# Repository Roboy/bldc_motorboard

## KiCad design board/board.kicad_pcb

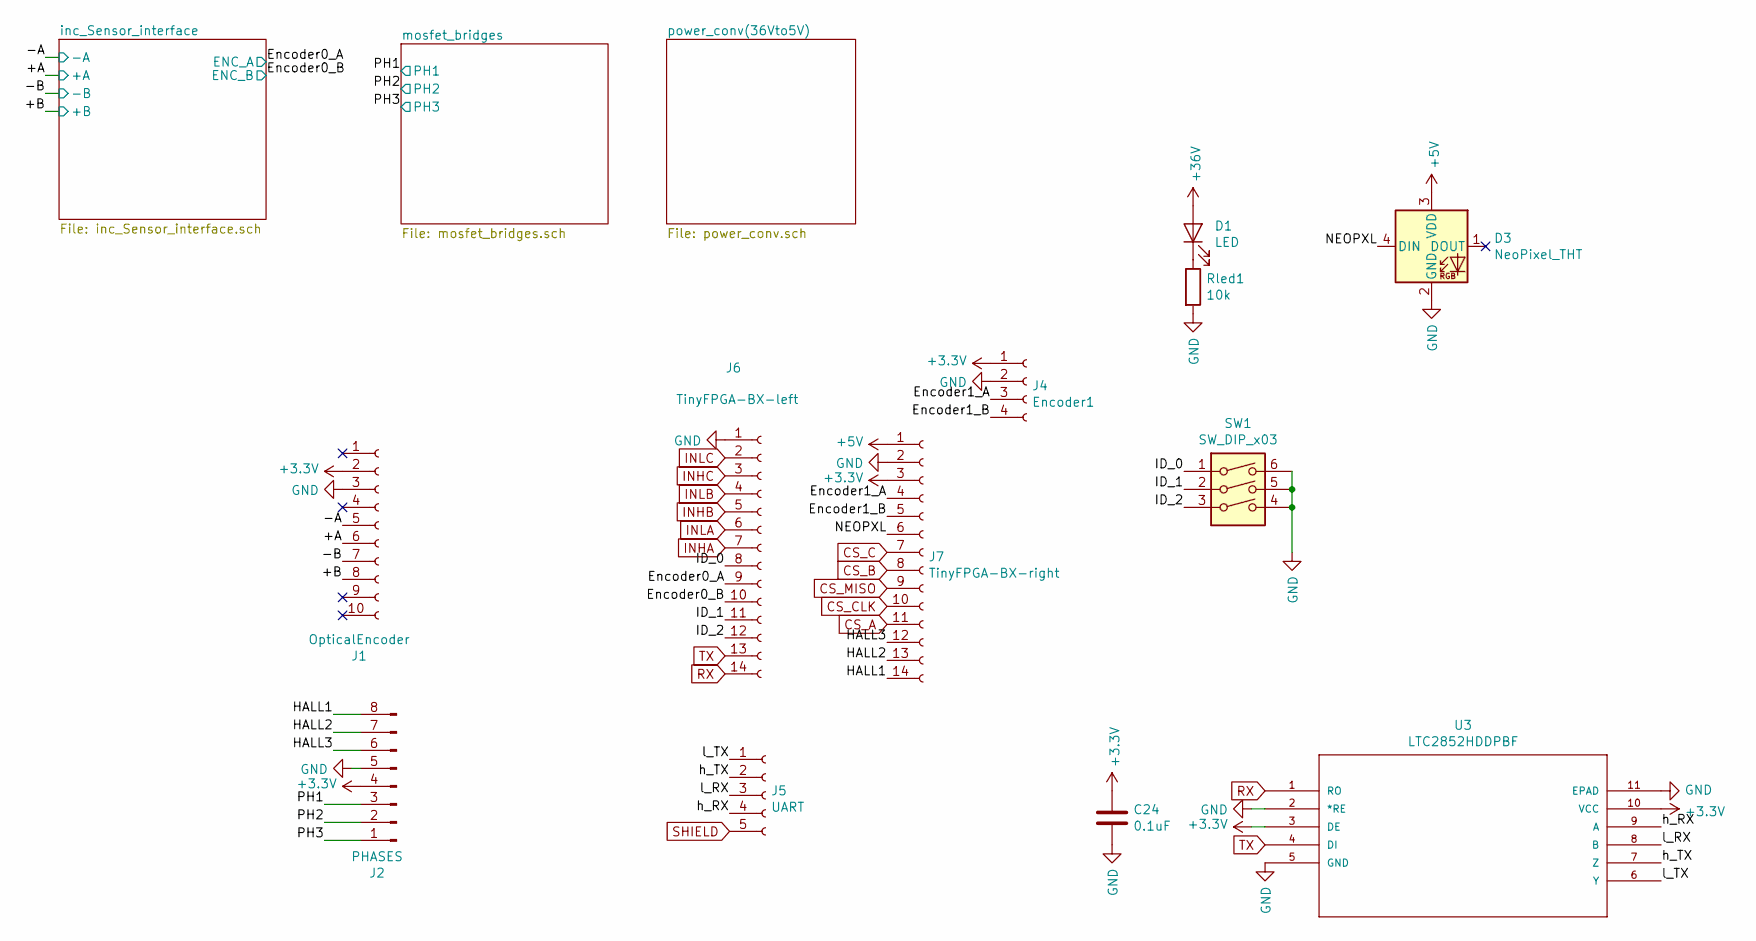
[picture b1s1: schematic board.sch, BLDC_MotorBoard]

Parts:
C24: 0.1uF; C_0402_1005Metric
D1: LED; C_0603_1608Metric_Pad1.05x0.95mm_HandSolder
D3: NeoPixel_THT; LED_WS2812B-PLCC4_3.5x3.5
J1: OpticalEncoder; MIRCO_MATCH
J2: PHASES; PinHeader_1x08_P2.54mm_Vertical
J4: Encoder1; TE-Connectivity_Micro-Match_connector_02x02_Pitch_1.27mm
J5: UART; TE-Connectivity_Micro-Match_connector_02x03_Pitch_1.27mm
J6: TinyFPGA-BX-left; PinSocket_1x14_P2.54mm_Vertical
J7: TinyFPGA-BX-right; PinSocket_1x14_P2.54mm_Vertical
Rled1: 10k; R_0402_1005Metric
SW1: SW_DIP_x03; SW_DIP_SPSTx03_Slide_KingTek_DSHP03TS_W7.62mm_P1.27mm
U3: LTC2852HDDPBF; LTC8252_DD_DFN-10_DD

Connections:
+3V3: C24.1, J1.2, J2.4, J4.1, J7.3, U3.3 (DE), U3.10 (VCC); also elsewhere on the board
+5V: D3.3 (VDD), J7.1; also elsewhere on the board
+36V: D1.2 (A); also elsewhere on the board
/+A: J1.6; also elsewhere on the board
/+B: J1.8; also elsewhere on the board
/-A: J1.5; also elsewhere on the board
/-B: J1.7; also elsewhere on the board
/Encoder0_A: J6.9; also elsewhere on the board
/Encoder0_B: J6.10; also elsewhere on the board
/Encoder1_A: J4.3, J7.4
/Encoder1_B: J4.4, J7.5
/HALL1: J2.8, J7.14
/HALL2: J2.7, J7.13
/HALL3: J2.6, J7.12
/ID_0: J6.8, SW1.1
/ID_1: J6.11, SW1.2
/ID_2: J6.12, SW1.3
/NEOPXL: D3.4 (DIN), J7.6
/PH1: J2.3; also elsewhere on the board
/PH2: J2.2; also elsewhere on the board
/PH3: J2.1; also elsewhere on the board
/h_RX: J5.4, U3.9 (A)
/h_TX: J5.2, U3.7 (Z)
/l_RX: J5.3, U3.8 (B)
/l_TX: J5.1, U3.6 (Y)
CS_A: J7.11; also elsewhere on the board
CS_B: J7.8; also elsewhere on the board
CS_C: J7.7; also elsewhere on the board
CS_CLK: J7.10; also elsewhere on the board
CS_MISO: J7.9; also elsewhere on the board
GND: C24.2, D3.2 (GND), J1.3, J2.5, J4.2, J6.1, J7.2, Rled1.2, SW1.4, SW1.5, SW1.6, U3.2 (*RE), U3.5 (GND), U3.11 (EPAD); also elsewhere on the board
INHA: J6.7; also elsewhere on the board
INHB: J6.5; also elsewhere on the board
INHC: J6.3; also elsewhere on the board
INLA: J6.6; also elsewhere on the board
INLB: J6.4; also elsewhere on the board
INLC: J6.2; also elsewhere on the board
unnamed: D1.1 (K), Rled1.1
RX: J6.14, U3.1 (RO)
SHIELD: J5.5
TX: J6.13, U3.4 (DI)

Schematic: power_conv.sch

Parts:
C8: 0.1uF; C_0402_1005Metric
C9, C10, C11, C12: 22u; C_0402_1005Metric
Rfb1: 45.6k; R_0402_1005Metric
Rt1: 22k; R_0402_1005Metric
U1: LTM8074; BGA-25_6.35x6.35mm_Layout5x5_P1.27mm

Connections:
+5V: C9.1, C10.1, C11.1, C12.1, U1.E1, U1.E2; also elsewhere on the board
+36V: C8.1, U1.A2, U1.A3, U1.A4; also elsewhere on the board
GND: C8.2, C9.2, C10.2, C11.2, C12.2, Rfb1.2, Rt1.2, U1.A1, U1.A5, U1.B2, U1.B3, U1.B4, U1.C2, U1.C3, U1.C4, U1.D2, U1.D3, U1.D4, U1.D5, U1.E3, U1.E4, U1.E5; also elsewhere on the board
unnamed: Rfb1.1, U1.D1
unnamed: Rt1.1, U1.B5

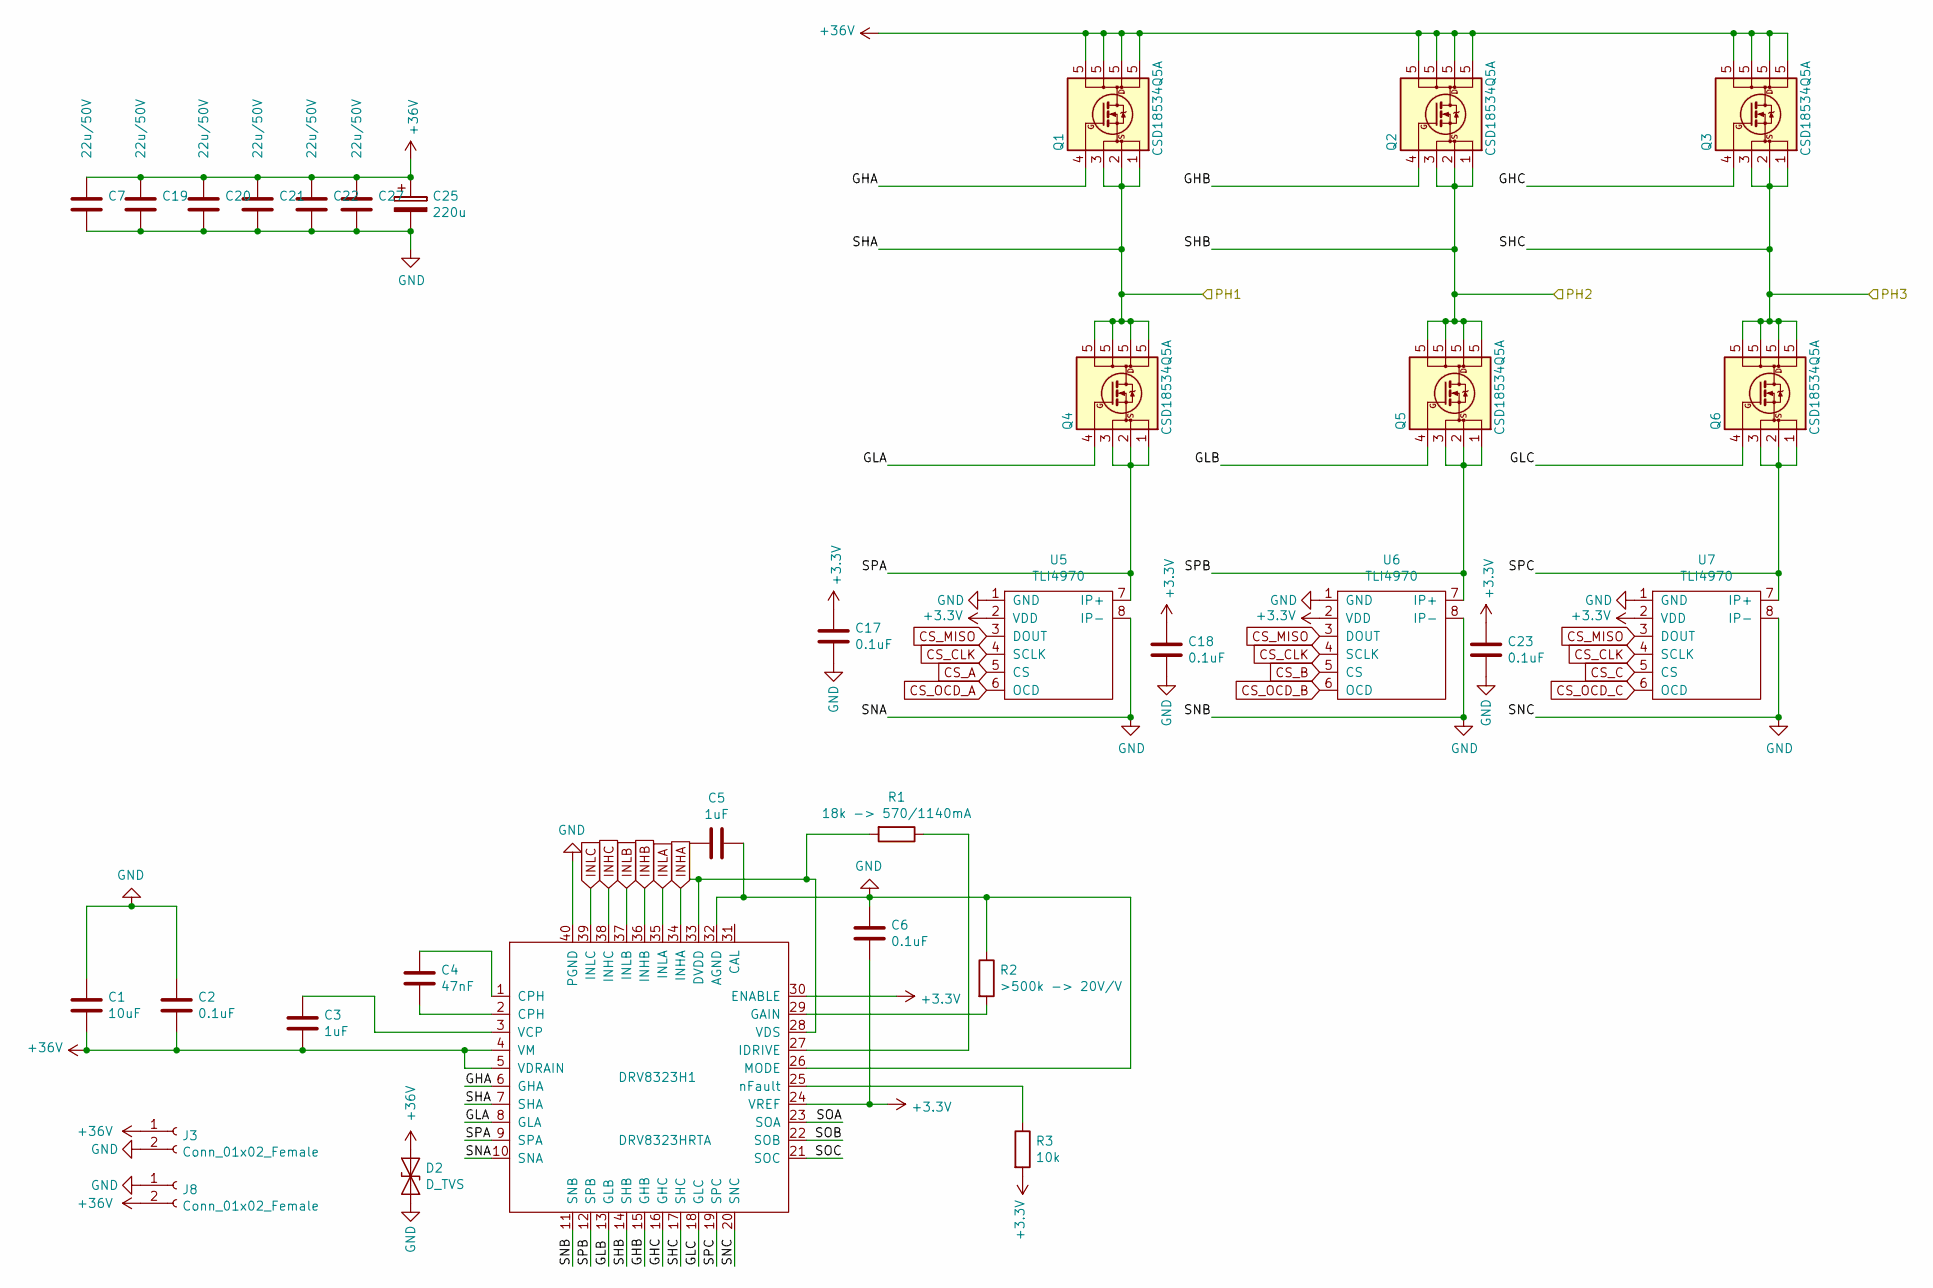
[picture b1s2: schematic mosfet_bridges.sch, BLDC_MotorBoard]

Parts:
C1: 10uF; C_0402_1005Metric
C2, C6, C17, C18, C23: 0.1uF; C_0402_1005Metric
C3, C5: 1uF; C_0402_1005Metric
C4: 47nF; C_0402_1005Metric
C7, C19, C20, C21, C22, C27: 22u/50V; C_0805_2012Metric
C25: 220u; CP_Elec_6.3x4.5
D2: D_TVS; D_0603_1608Metric
DRV8323H1: DRV8323HRTA; QFN-40-1EP_6x6mm_Pitch0.5mm
J3, J8: Conn_01x02_Female; Wago_2060_2_SMD
Q1, Q2, Q3, Q4, Q5, Q6: CSD18534Q5A; VSON-8_3.3x3.3mm_P0.65mm_NexFET
R1: 18k -> 570/1140mA; R_0402_1005Metric
R2: >500k -> 20V/V; R_0402_1005Metric
R3: 10k; R_0402_1005Metric
U5, U6, U7: TLI4970

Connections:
+3V3: C6.2, C17.1, C18.1, C23.1, DRV8323H1.24 (VREF), DRV8323H1.30 (ENABLE), R3.2, U5.2 (VDD), U6.2 (VDD), U7.2 (VDD); also elsewhere on the board
+36V: C1.2, C2.2, C3.2, C7.1, C19.1, C20.1, C21.1, C22.1, C25.1, C27.1, D2.1 (A1), DRV8323H1.4 (VM), DRV8323H1.5 (VDRAIN), J3.1, J8.2, Q1.5 (D), Q2.5 (D), Q3.5 (D); also elsewhere on the board
/PH1: DRV8323H1.7 (SHA), Q1.1 (S), Q1.2 (S), Q1.3 (S), Q4.5 (D); also elsewhere on the board
/PH2: DRV8323H1.14 (SHB), Q2.1 (S), Q2.2 (S), Q2.3 (S), Q5.5 (D); also elsewhere on the board
/PH3: DRV8323H1.17 (SHC), Q3.1 (S), Q3.2 (S), Q3.3 (S), Q6.5 (D); also elsewhere on the board
/mosfet_bridges/GHA: DRV8323H1.6 (GHA), Q1.4 (G)
/mosfet_bridges/GHB: DRV8323H1.15 (GHB), Q2.4 (G)
/mosfet_bridges/GHC: DRV8323H1.16 (GHC), Q3.4 (G)
/mosfet_bridges/GLA: DRV8323H1.8 (GLA), Q4.4 (G)
/mosfet_bridges/GLB: DRV8323H1.13 (GLB), Q5.4 (G)
/mosfet_bridges/GLC: DRV8323H1.18 (GLC), Q6.4 (G)
/mosfet_bridges/SOA: DRV8323H1.23 (SOA)
/mosfet_bridges/SOB: DRV8323H1.22 (SOB)
/mosfet_bridges/SOC: DRV8323H1.21 (SOC)
/mosfet_bridges/SPA: DRV8323H1.9 (SPA), Q4.1 (S), Q4.2 (S), Q4.3 (S), U5.7 (IP+)
/mosfet_bridges/SPB: DRV8323H1.12 (SPB), Q5.1 (S), Q5.2 (S), Q5.3 (S), U6.7 (IP+)
/mosfet_bridges/SPC: DRV8323H1.19 (SPC), Q6.1 (S), Q6.2 (S), Q6.3 (S), U7.7 (IP+)
CS_A: U5.5 (CS); also elsewhere on the board
CS_B: U6.5 (CS); also elsewhere on the board
CS_C: U7.5 (CS); also elsewhere on the board
CS_CLK: U5.4 (SCLK), U6.4 (SCLK), U7.4 (SCLK); also elsewhere on the board
CS_MISO: U5.3 (DOUT), U6.3 (DOUT), U7.3 (DOUT); also elsewhere on the board
CS_OCD_A: U5.6 (OCD)
CS_OCD_B: U6.6 (OCD)
CS_OCD_C: U7.6 (OCD)
GND: C1.1, C2.1, C5.1, C6.1, C7.2, C17.2, C18.2, C19.2, C20.2, C21.2, C22.2, C23.2, C25.2, C27.2, D2.2 (A2), DRV8323H1.10 (SNA), DRV8323H1.11 (SNB), DRV8323H1.20 (SNC), DRV8323H1.26 (MODE), DRV8323H1.32 (AGND), DRV8323H1.40 (PGND), J3.2, J8.1, R2.1, U5.1 (GND), U5.8 (IP-), U6.1 (GND), U6.8 (IP-), U7.1 (GND), U7.8 (IP-); also elsewhere on the board
INHA: DRV8323H1.34 (INHA); also elsewhere on the board
INHB: DRV8323H1.36 (INHB); also elsewhere on the board
INHC: DRV8323H1.38 (INHC); also elsewhere on the board
INLA: DRV8323H1.35 (INLA); also elsewhere on the board
INLB: DRV8323H1.37 (INLB); also elsewhere on the board
INLC: DRV8323H1.39 (INLC); also elsewhere on the board
unnamed: C3.1, DRV8323H1.3 (VCP)
unnamed: C4.1, DRV8323H1.1 (CPH)
unnamed: C4.2, DRV8323H1.2 (CPH)
unnamed: C5.2, DRV8323H1.28 (VDS), DRV8323H1.33 (DVDD), R1.2
unnamed: DRV8323H1.25 (nFault), R3.1
unnamed: DRV8323H1.27 (IDRIVE), R1.1
unnamed: DRV8323H1.29 (GAIN), R2.2

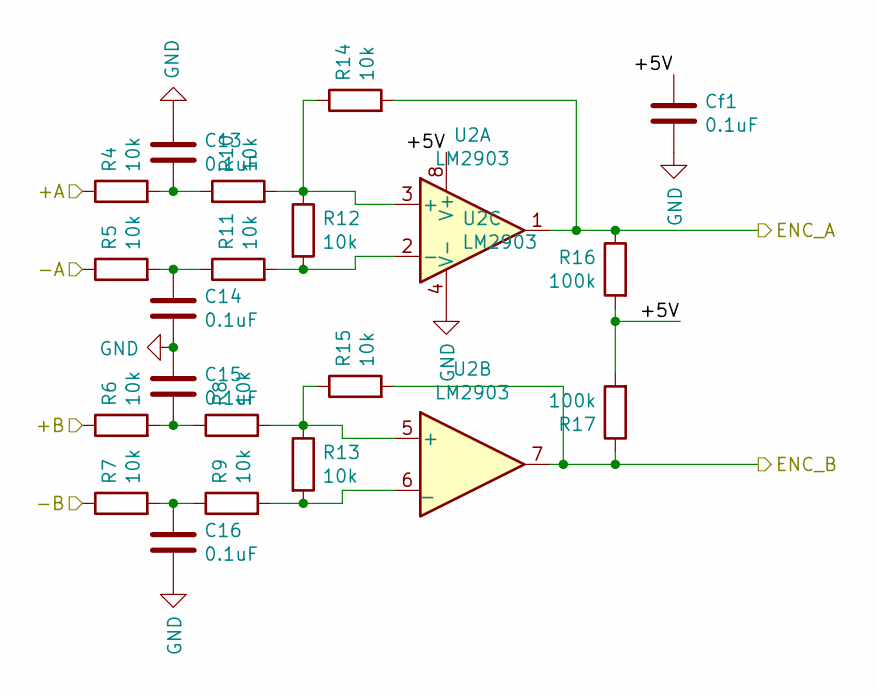
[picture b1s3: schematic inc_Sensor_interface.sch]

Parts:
C13, C14, C15, C16: 0.1uF; C_0402_1005Metric
Cf1: 0.1uF; C_0402_1005Metric
R4, R5, R6, R7, R8, R9, R10, R11, R12, R13, R14, R15: 10k; R_0402_1005Metric
R16, R17: 100k; R_0402_1005Metric
U2: LM2903; TSSOP-8_3x3mm_P0.65mm

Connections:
+3V3: Cf1.1, R16.2, R17.2, U2.8 (V+); also elsewhere on the board
/+A: R4.1; also elsewhere on the board
/+B: R6.1; also elsewhere on the board
/-A: R5.1; also elsewhere on the board
/-B: R7.1; also elsewhere on the board
/Encoder0_A: R14.2, R16.1, U2.1; also elsewhere on the board
/Encoder0_B: R15.2, R17.1, U2.7; also elsewhere on the board
GND: C13.1, C14.2, C15.1, C16.2, Cf1.2, U2.4 (V-); also elsewhere on the board
unnamed: C13.2, R4.2, R10.1
unnamed: C14.1, R5.2, R11.1
unnamed: C15.2, R6.2, R8.1
unnamed: C16.1, R7.2, R9.1
unnamed: R10.2, R12.1, R14.1, U2.3 (+)
unnamed: R11.2, R12.2, U2.2 (-)
unnamed: R8.2, R13.1, R15.1, U2.5 (+)
unnamed: R9.2, R13.2, U2.6 (_)

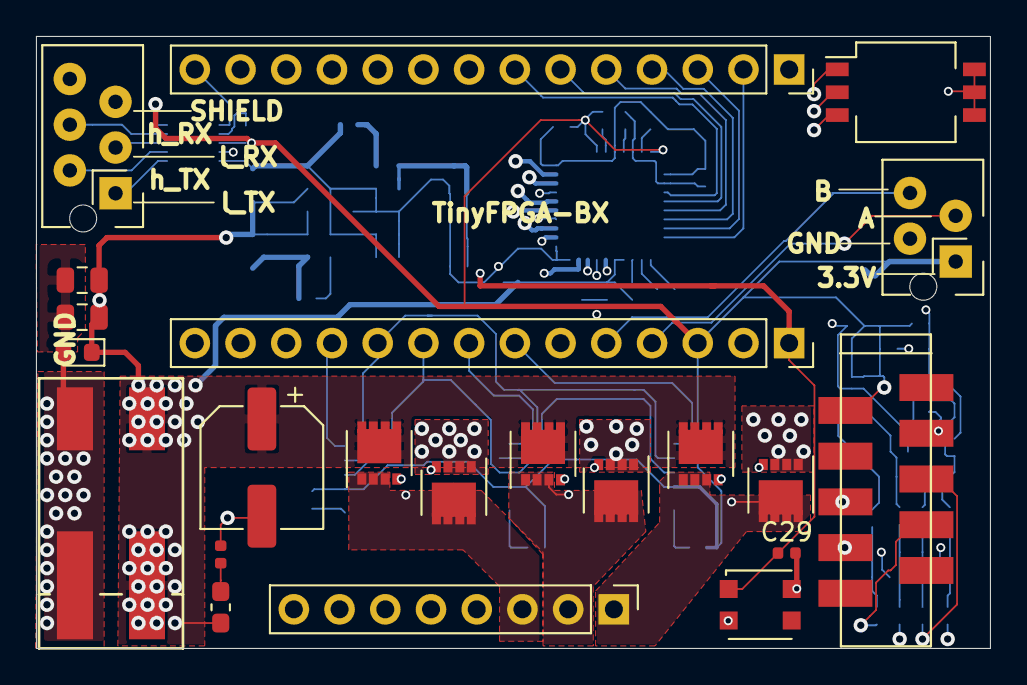
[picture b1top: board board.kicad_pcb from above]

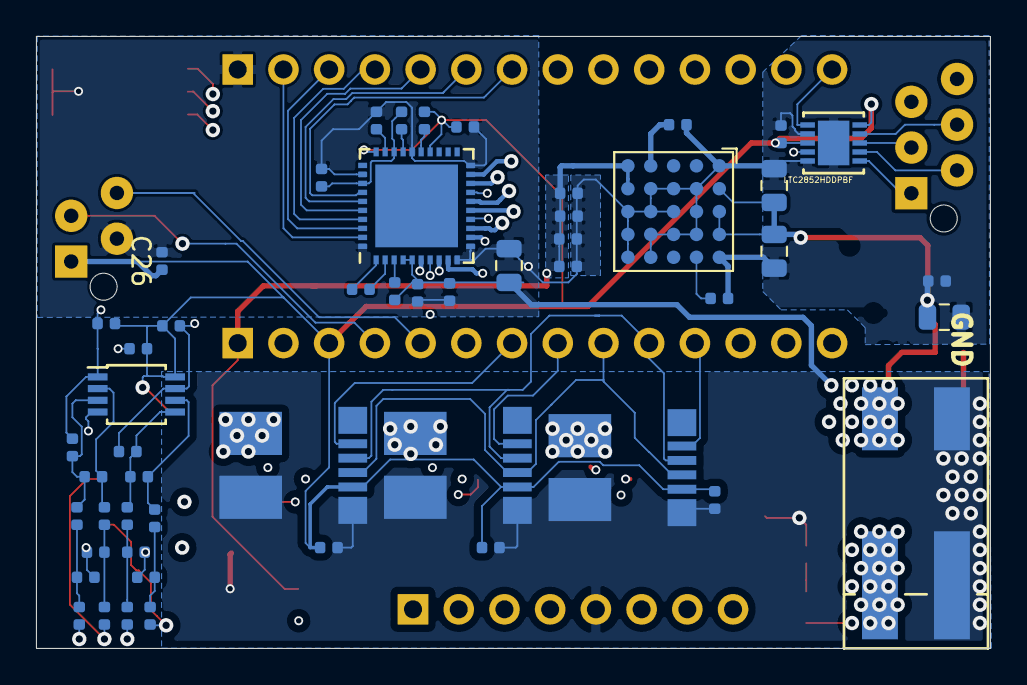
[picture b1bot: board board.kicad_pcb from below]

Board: 4 copper layers, 53.0 x 34.0 mm, 74 parts (52 on the bottom side), 66 nets.

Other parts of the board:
C26, C29: 0.1uF; C_0402_1005Metric

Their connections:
+3V3: C26.1; also elsewhere on the board
+5V: C29.1; also elsewhere on the board
GND: C26.2, C29.2; also elsewhere on the board

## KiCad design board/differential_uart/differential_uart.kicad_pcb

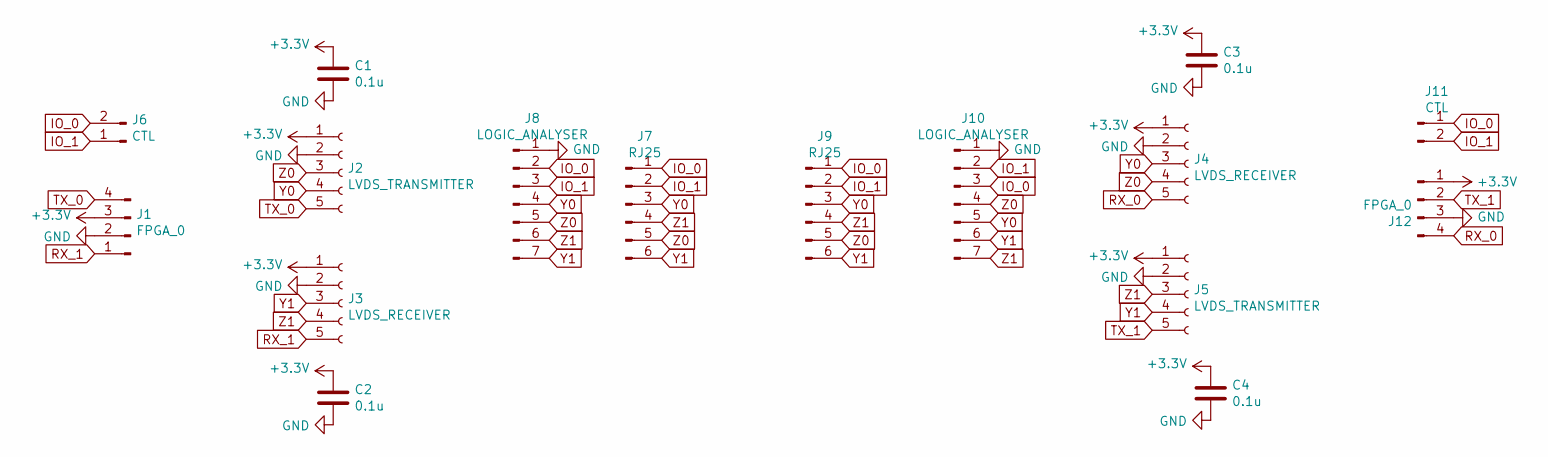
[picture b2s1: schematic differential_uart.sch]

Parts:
C1, C2, C3, C4: 0.1u; C_01005_0402Metric
J1, J12: FPGA_0; PinHeader_1x04_P2.54mm_Vertical
J2, J5: LVDS_TRANSMITTER; SOT-23-5
J3, J4: LVDS_RECEIVER; SOT-23-5
J6, J11: CTL; PinHeader_1x02_P2.54mm_Vertical
J7, J9: RJ25; RJ25-6p6c-5555154-1
J8, J10: LOGIC_ANALYSER; PinHeader_1x07_P2.54mm_Vertical

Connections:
+3V3: C1.1, C2.1, C3.1, C4.1, J1.3, J2.1, J3.1, J4.1, J5.1, J12.1
GND: C1.2, C2.2, C3.2, C4.2, J1.2, J2.2, J3.2, J4.2, J5.2, J7.7, J7.8, J8.1, J9.7, J9.8, J10.1, J12.3
IO_0: J6.2, J7.1, J8.2, J9.1, J10.3, J11.1
IO_1: J6.1, J7.2, J8.3, J9.2, J10.2, J11.2
RX_0: J4.5, J12.4
RX_1: J1.1, J3.5
TX_0: J1.4, J2.5
TX_1: J5.5, J12.2
Y0: J2.4, J4.3, J7.3, J8.4, J9.3, J10.5
Y1: J3.3, J5.4, J7.6, J8.7, J9.6, J10.6
Z0: J2.3, J4.4, J7.5, J8.5, J9.5, J10.4
Z1: J3.4, J5.3, J7.4, J8.6, J9.4, J10.7

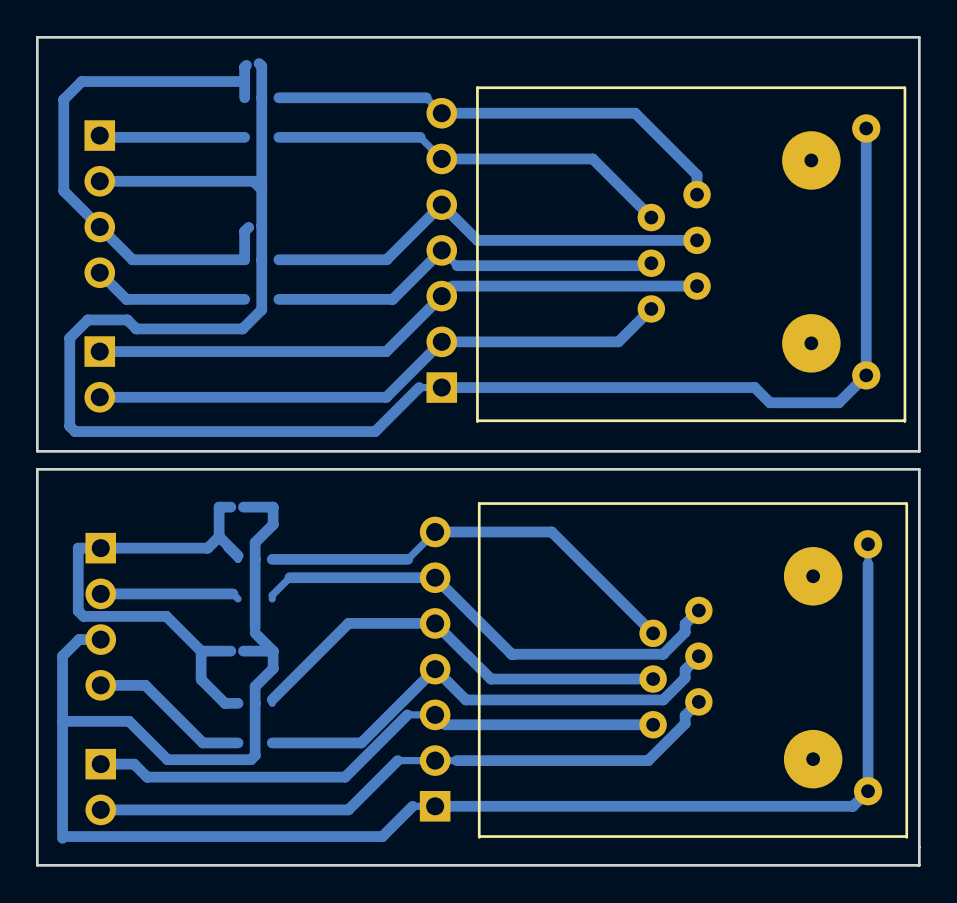
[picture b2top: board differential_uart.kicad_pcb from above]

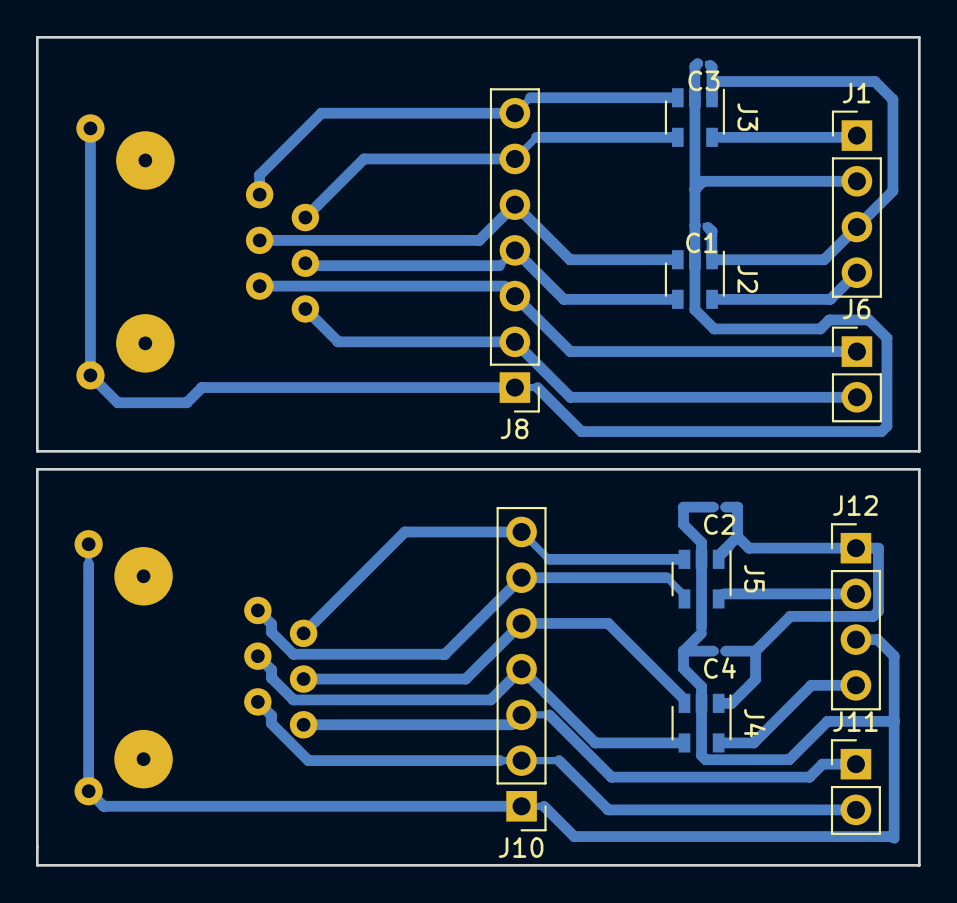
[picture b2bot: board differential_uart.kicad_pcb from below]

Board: 2 copper layers, 49.0 x 46.0 mm, 16 parts (14 on the bottom side), 12 nets.

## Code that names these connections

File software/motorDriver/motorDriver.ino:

int INHA = 0;
int INLA = 1;
int INHB = 2;
int INLB = 3;
int INHC = 4;
int INLC = 5;
int HALLA = A4;
int HALLB = A5;
int HALLC = A6;

int order[] = {INHA,INLA,INHB,INLB,INHC,INLC};
int a[] = {1,0,0,1,0,0};
int b[] = {1,0,0,0,0,1};
int c[] = {0,0,1,0,0,1};
int d[] = {0,1,1,0,0,0};
int e[] = {0,1,0,0,1,0};
int f[] = {0,0,0,1,1,0};

// the setup routine runs once when you press reset:
void setup() {
  // initialize the digital pin as an output.
  pinMode(INHA, OUTPUT);
  pinMode(INHB, OUTPUT);
  pinMode(INHC, OUTPUT);
  pinMode(INLA, OUTPUT);
  pinMode(INLB, OUTPUT);
  pinMode(INLC, OUTPUT);
  pinMode(HALLA, INPUT_PULLUP);
  pinMode(HALLB, INPUT_PULLUP);
  pinMode(HALLC, INPUT_PULLUP);
  digitalWrite(INHA, LOW);   
  digitalWrite(INLA, LOW);
  digitalWrite(INHB, LOW);   
  digitalWrite(INLB, LOW); 
  digitalWrite(INHC, LOW);   
  digitalWrite(INLC, LOW);  
  Serial.begin(115200);
}



// the loop routine runs over and over again forever:
void loop() {
  char str[100];
  bool hall1 = digitalRead(HALLA);
  bool hall2 = digitalRead(HALLB);
  bool hall3 = digitalRead(HALLC);
//  sprintf(str, "%d %d %d", hall1, hall2, hall3);
//  Serial.println(str);
  if(hall1==true && hall2 == false && hall3 == true){
    for(int i=0;i<6;i++){
      digitalWrite(order[i], a[i]);
    }
//    Serial.println("a");
  }
  if(hall1==true && hall2 == false && hall3 == false){
    for(int i=0;i<6;i++){
      digitalWrite(order[i], b[i]);
    }
//    Serial.println("b");
  }
  if(hall1==true && hall2 == true && hall3 == false){
    for(int i=0;i<6;i++){
      digitalWrite(order[i], c[i]);
    }
//    Serial.println("c");
  }
  if(hall1==false && hall2 == true && hall3 == false){
    for(int i=0;i<6;i++){
      digitalWrite(order[i], d[i]);
    }
//    Serial.println("d");
  }
  if(hall1==false && hall2 == true && hall3 == true){
    for(int i=0;i<6;i++){
      digitalWrite(order[i], e[i]);
    }
//    Serial.println("e");
  }
  if(hall1==false && hall2 == false && hall3 == true){
    for(int i=0;i<6;i++){
      digitalWrite(order[i], f[i]);
    }
//    Serial.println("f");
  }
//  digitalWrite(INHA, HIGH);   
//  digitalWrite(INLA, LOW); 
//  delay(10);
//  digitalWrite(INHA, LOW);   
//  digitalWrite(INLA, HIGH); 
//  delay(10);
//  digitalWrite(INHB, HIGH);   
//  digitalWrite(INLB, LOW); 
//  delay(10);
//  digitalWrite(INHB, LOW);   
//  digitalWrite(INLB, HIGH); 
//  delay(10);
//  digitalWrite(INHC, HIGH);   
//  digitalWrite(INLC, LOW); 
//  delay(10);
//  digitalWrite(INHC, LOW);   
//  digitalWrite(INLC, HIGH); 
    
}

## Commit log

2019-06-15 initial
2019-06-15 with ice
2019-06-16 pretty
2019-06-16 layout partially done
2019-06-30 layout done
2019-06-30 layout done, ordered on ailser
2019-07-09 with spi driver
2019-07-09 with flash adapter
2019-08-01 with correct clock footprint
2019-08-02 done
2019-08-04 increased clearance
2019-08-15 working on schematics
2019-08-15 more datasheets
2019-08-19 with diff uart prototype
2019-08-20 more code motherfuckers
2019-08-21 started design
2019-08-23 with uart draft
2019-08-24 uart draft works
2019-08-24 magic number works
2019-08-24 draft crc checksum
2019-08-24 with crc draft
2019-08-25 placement
2019-08-25 with 115200 baurate
2019-08-25 with 20byte frames at 4MHz baudrate using 620 ohm pullups
2019-08-26 added dcdc converter
2019-08-28 added CAN transreciever
2019-08-29 first pcb layout
2019-08-31 removed superfluous stufdf
2019-08-31 with dip switch
2019-09-01 3.3V for second encoder+micromatch
2019-09-02 revision prototype 0
2019-09-03 ordered on aisler
2019-09-10 with bom
2019-09-12 with uart_tx uart_rx
2019-09-12 with status frame request and response
2019-09-12 the frame matcher needs to have a dedicated fifo
2019-09-12 status frame works
2019-09-12 setpoint controlmode and status working
2019-09-12 with protocol description
2019-09-12 and the motor turns :P
2019-09-12 with pd controller and position control
2019-09-13 never miss a tick again
2019-09-13 faster
2019-09-15 with datasheets for 500N motor
2019-09-15 fix crc checksum and only react to id for me
2019-09-16 with tli5012b datasheet
2019-09-16 better
2019-09-16 fixed communication
2019-09-17 holy moses
2019-09-18 communication works
2019-09-19 with velocity measurements
2019-09-19 with current sensor readout draft
2019-09-19 clean up
